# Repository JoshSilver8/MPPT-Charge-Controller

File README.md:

# MPPT-Charge-Controller

**Introduction** | This project was created in the scope of the the class ENGR 460 "Power Engineering" conducted through online learning at Walla Walla University. I was tasked with designing, building, and testing a *Solar Charge Controller*. For more information on the theory and circuit analysis of the design, please refer to the "Wiki" tab.

**Navigation** | This repository consists of several folders. In this "code" tab, you will find 2 main folders: Arduino & KiCAD. Within the Arduino file, you will find a folder containing the code that the charge controller runs on. The KiCAD folder contains the KiCAD project zip file which can be used to replicate the board used in this project

**Results** | The Charge Controller is in working order, there are some bugs with the Display output, and the board has to be slightly modified in this intial revision of the board. For more details visit the "Wiki" tab where the final indepth report is given.

**Status of Project** | Visit the "issues" tab to see errors and fixes for this project - which should provide a more in depth explanation for the quote "status" of the project. Can also visit the "Wiki" page or view the documentation files in the folders for a description of build and test process when troubleshooting issues.

**Credit** | This project was not without help, I would like to thank [Opengreenenergy](https://www.instructables.com/id/ARDUINO-SOLAR-CHARGE-CONTROLLER-Version-30/) for their charge controller design which helped me understand how to go about designing my controller. I referenced there block diagram and schematic. this was a great resource to start designing and understanding MPPT early in the project especially in the design of the Synchonous Buck Converter and upon looking at the two side my side after the fact they are more alike than I realized or wanted, this is likely due to choosing the same mosfets and mosfet driver which lookeed like a really good fit for my project, and after following the datasheets specification for those parts (whcih I can only assume that Opengreenenergy did the same) they looked similar when paired with the buck converter design used. however, it was too late in the project to make any radical design changes to revent the wheel. <br />
I'd also like to include [Tim Knowlan](https://github.com/Elexy/SerettaLabs/blob/master/mpptControler/ppt.pde) for allowing me to sample his code for this project. I needed to do some more editting to really squish out all the bugs I'm finding but I believe I was able to get the mosfets driving properly with this code indicated by the fact that I was getting 13.9V on testing which is within the maximum voltage out according the code. However, I have been unable to get the peripherals to function properly (LED's and I2C Display), this will hopefully be resolved in a future update (see Issues).

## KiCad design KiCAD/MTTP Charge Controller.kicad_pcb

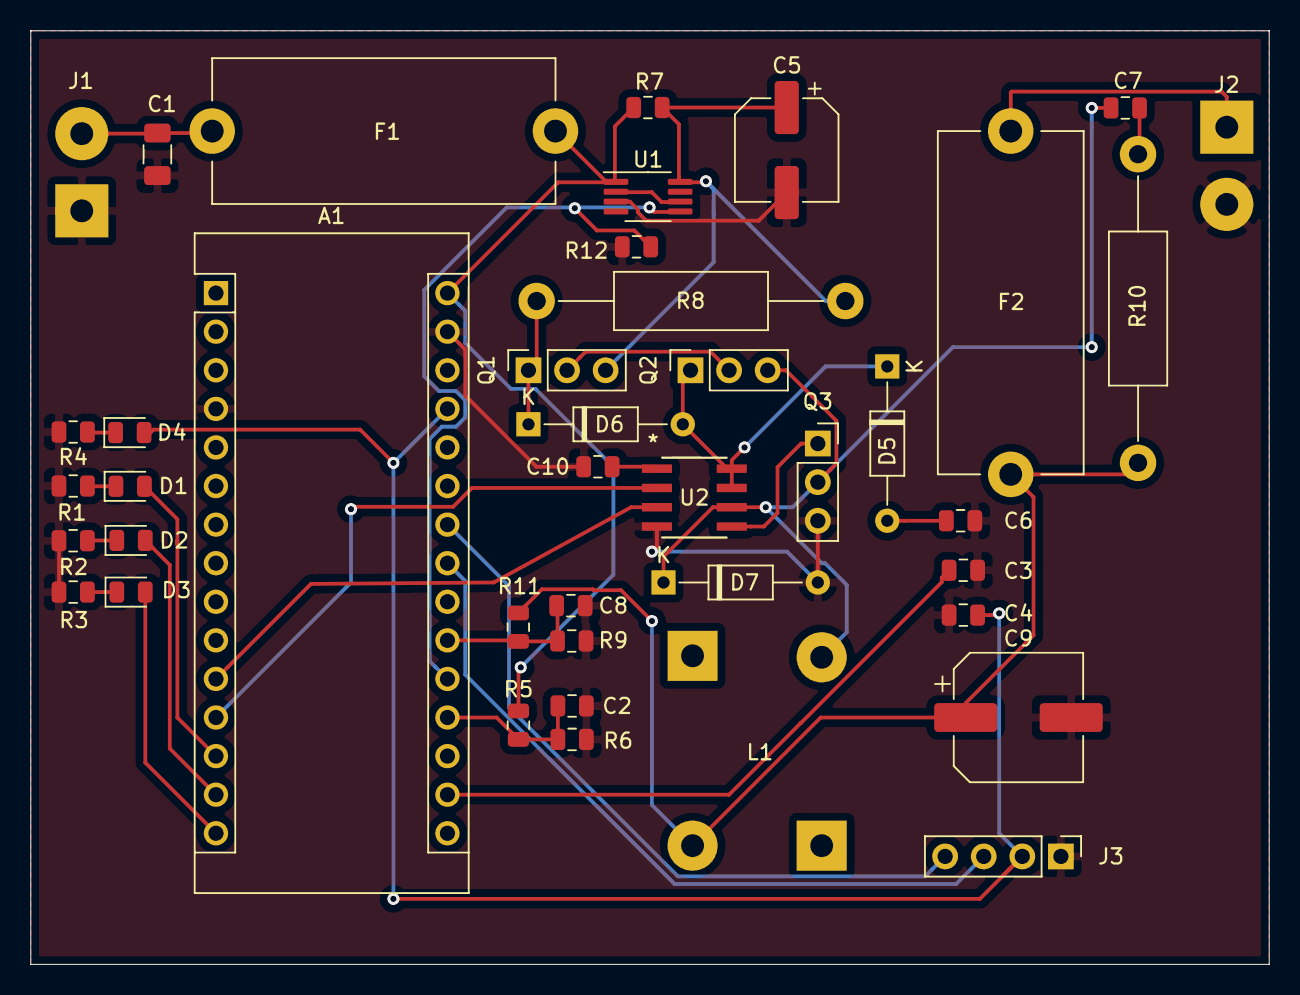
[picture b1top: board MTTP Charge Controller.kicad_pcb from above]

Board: 2 copper layers, 81.5 x 61.5 mm, 41 parts (0 on the bottom side), 30 nets.

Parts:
A1: Arduino_Nano_v3.x; Arduino_Nano
C1: 1uF; C_1206_3216Metric
C2, C3, C4, C6, C7, C8, C10: .1uF; C_0805_2012Metric
C5: 100uF; CP_Elec_6.3x5.9
C9: 220uF; CP_Elec_8x6.9
D1: Green_On; LED_0805_2012Metric
D2: Yellow_Buck; LED_0805_2012Metric
D3: Red_Off; LED_0805_2012Metric
D4: Blue_PWR; LED_0805_2012Metric
D5, D6, D7: 1N4148; D_DO-35_SOD27_P10.16mm_Horizontal
F1, F2: 10A; Fuseholder_Cylinder-5x20mm_Stelvio-Kontek_PTF78_Horizontal_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
J1: PV Connection; SolderWirePad_1x02_P5.08mm_Drill1.5mm
J2: 12V Out; SolderWirePad_1x02_P5.08mm_Drill1.5mm
J3: I2C Display; PinHeader_1x04_P2.54mm_Vertical
L1: 33uH; DEP1519b_Inductor
Q1, Q2, Q3: IRFIZ44N; PinSocket_1x03_P2.54mm_Vertical
R1, R2, R3, R4: 330; R_0805_2012Metric
R5, R11: 10k; R_0805_2012Metric
R6, R9: 2.2k; R_0805_2012Metric
R7: 0.01; R_0805_2012Metric
R8, R10: 470K; R_Axial_DIN0411_L9.9mm_D3.6mm_P20.32mm_Horizontal
R12: 100K; R_0805_2012Metric
U1: AD8212; MSOP-8_3x3mm_P0.65mm
U2: IR2104; IR2104SPBF

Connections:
/3.3V: A1.17, C3.1
/5V: A1.27, C4.2, D4.2, J3.2
/ISense: A1.20, R12.2, U1.5
/PWM: A1.12, U2.2
/PWM_EN: A1.11, U2.3
/SCL: A1.24, J3.4
/SDA: A1.23, J3.3
/VIN: A1.30, C10.2, F1.1, R5.1, R7.2, U1.1, U2.1
/VinSense: A1.19, C2.2, R5.2, R6.1
/VoutSense: A1.21, C8.1, R9.1, R11.2
GND: A1.4, A1.29, C1.1, C2.1, C3.2, C4.1, C5.2, C6.1, C8.2, C9.2, C10.1, D7.2, J1.1, J2.2, J3.1, Q3.3, R1.2, R2.2, R3.2, R4.2, R6.2, R9.2, R12.1, U1.3, U2.4
unnamed: A1.13, D1.2
unnamed: A1.14, D2.2
unnamed: A1.15, D3.2
unnamed: C1.2, F1.2, J1.2
unnamed: C5.1, Q1.3, R7.1, R8.1, U1.8
unnamed: C6.2, D5.2
unnamed: C7.1, D7.1, L1.1, Q2.3, Q3.2, U2.6
unnamed: C7.2, R10.1
unnamed: C9.1, F2.2, L1.2, R10.2, R11.1
unnamed: D1.1, R1.1
unnamed: D2.1, R2.1
unnamed: D3.1, R3.1
unnamed: D4.1, R4.1
unnamed: D5.1, D6.2, Q2.1, U2.7, U2.8
unnamed: D6.1, Q1.1, R8.2
unnamed: F2.1, J2.1
unnamed: Q1.2, Q2.2
unnamed: Q3.1, U2.5
unnamed: U1.2, U1.6

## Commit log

2020-06-09 Create MPPT_Charge_Controller_Final_Code

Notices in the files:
parts and their libraries:
Copyright 2016 Accelerated Designs. All rights reserved.
